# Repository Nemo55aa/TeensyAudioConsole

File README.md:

# TeensyAudioConsole
TeensyAudioConsole is a board that allows TeensyAudio to be used like a gadget such as a guitar pedal or synth module. 
I wanted to use something like that myself, and I also wanted to increase TeensyAudio's value as an instrument.
# HowtoUse
TeensyAudio's basic usage is Here:
https://www.pjrc.com/teensy/td_libs_Audio.html

# TeensyAudioConsole
TeensyAudioの，エフェクターやシンセモジュラーのようなガジェットとしての価値を高めるために作りました．
現在発注中なので，届き次第詳しい使い方についてまとめます．

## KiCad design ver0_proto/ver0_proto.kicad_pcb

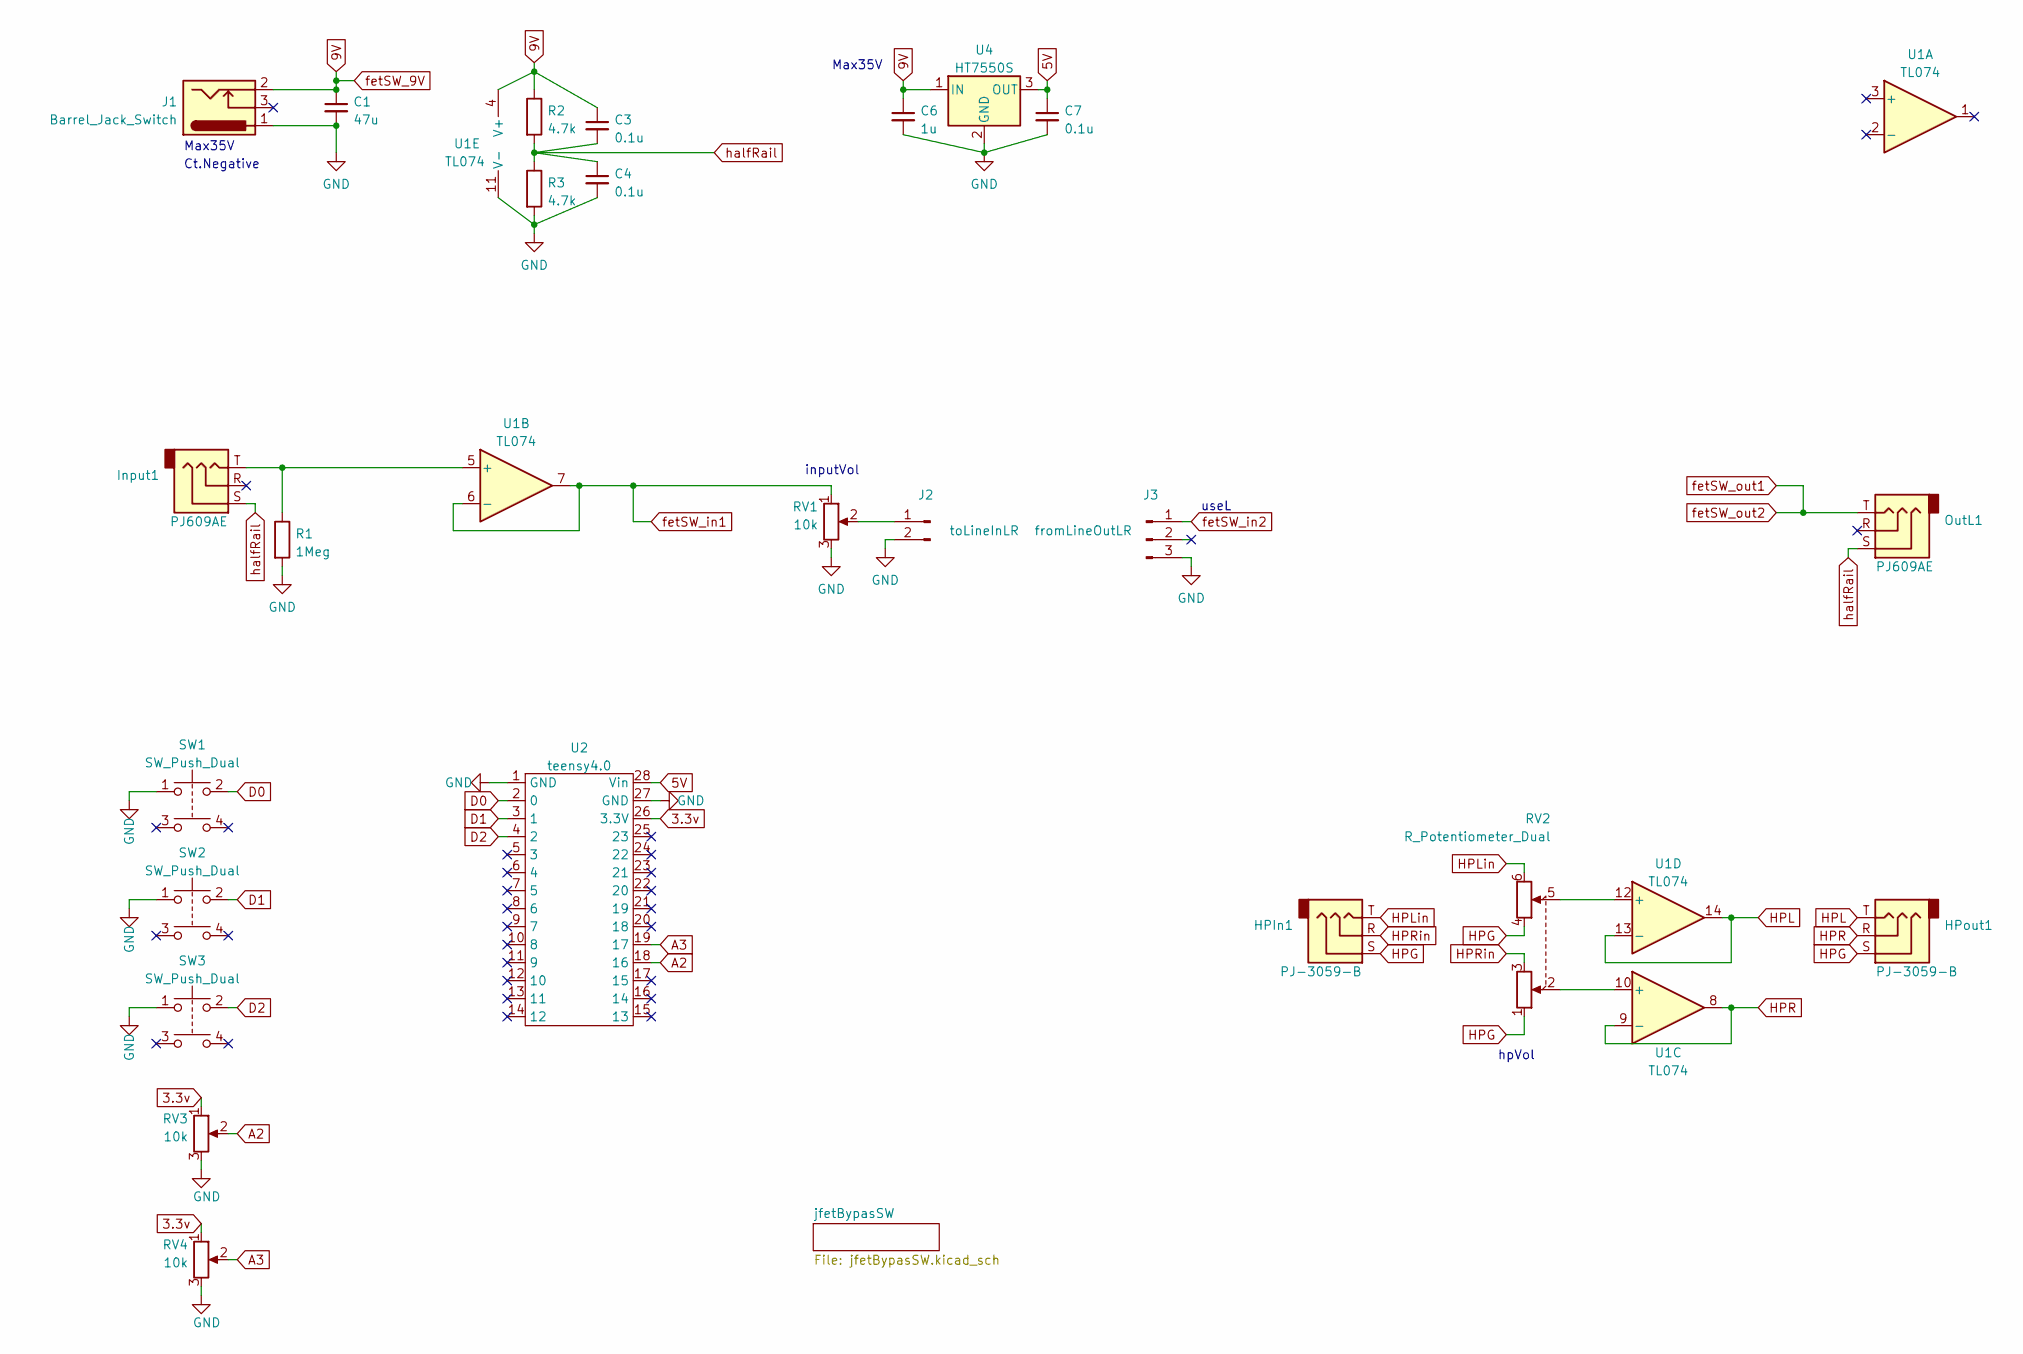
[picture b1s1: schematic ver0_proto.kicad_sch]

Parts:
C1: 47u; CP_Radial_D10.0mm_P2.50mm_P5.00mm
C3, C4, C7: 0.1u; C_0603_1608Metric_Pad1.08x0.95mm_HandSolder
C6: 1u; C_0603_1608Metric_Pad1.08x0.95mm_HandSolder
HPIn1: PJ-3059-B; AUDIO-TH_XKB_PJ-3059-B
HPout1: PJ-3059-B; AUDIO-TH_XKB_PJ-3059-B
Input1: PJ609AE; AUDIO-TH_PJ-609AE
J1: Barrel_Jack_Switch; BarrelJack_Horizontal
J2: toLineInLR; PinHeader_1x02_P2.54mm_Vertical
J3: fromLineOutLR; PinHeader_1x03_P2.54mm_Vertical
OutL1: PJ609AE; AUDIO-TH_PJ-609AE
R1: 1Meg; R_0603_1608Metric_Pad0.98x0.95mm_HandSolder
R2, R3: 4.7k; R_0603_1608Metric_Pad0.98x0.95mm_HandSolder
RV1, RV3, RV4: 10k; RES-TH_RK09K1130AAU
RV2: R_Potentiometer_Dual; RES-TH_RK14K1240036
SW1, SW2, SW3: SW_Push_Dual; SW_PUSH_6mm
U1: TL074; SO-14_3.9x8.65mm_P1.27mm
U2: teensy4.0; teensy4.0WithAudioSh
U4: HT7550S; SOT-23

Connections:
3.3v: RV3.1, RV4.1, U2.26 (3.3V)
5V: C7.1, U2.28 (Vin), U4.3 (OUT)
9V: C1.1, C3.1, C6.1, J1.2, R2.1, U1.4 (V+), U4.1 (IN); also elsewhere on the board
A2: RV3.2, U2.18 (16)
A3: RV4.2, U2.19 (17)
D0: SW1.2, U2.2 (0)
D1: SW2.2, U2.3 (1)
D2: SW3.2, U2.4 (2)
GND: C1.2, C4.2, C6.2, C7.2, J1.1, J2.2, J3.3, R1.2, R3.2, RV1.3, RV3.3, RV4.3, SW1.1, SW2.1, SW3.1, U1.11 (V-), U2.1 (GND), U2.27 (GND), U4.2 (GND); also elsewhere on the board
HPG: HPIn1.S, HPout1.S, RV2.1, RV2.4
HPL: HPout1.T, U1.13 (-), U1.14
HPLin: HPIn1.T, RV2.6
HPR: HPout1.R, U1.8, U1.9 (-)
HPRin: HPIn1.R, RV2.3
unnamed: Input1.T, R1.1, U1.5 (+)
unnamed: J2.1, RV1.2
unnamed: RV2.5, U1.12 (+)
unnamed: RV2.2, U1.10 (+)
fetSW_in1: RV1.1, U1.6 (-), U1.7; also elsewhere on the board
fetSW_in2: J3.1; also elsewhere on the board
fetSW_out1: OutL1.T; also elsewhere on the board
halfRail: C3.2, C4.1, Input1.S, OutL1.S, R2.2, R3.1

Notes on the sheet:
Max35V
useL
inputVol
hpVol
Ct.Negative

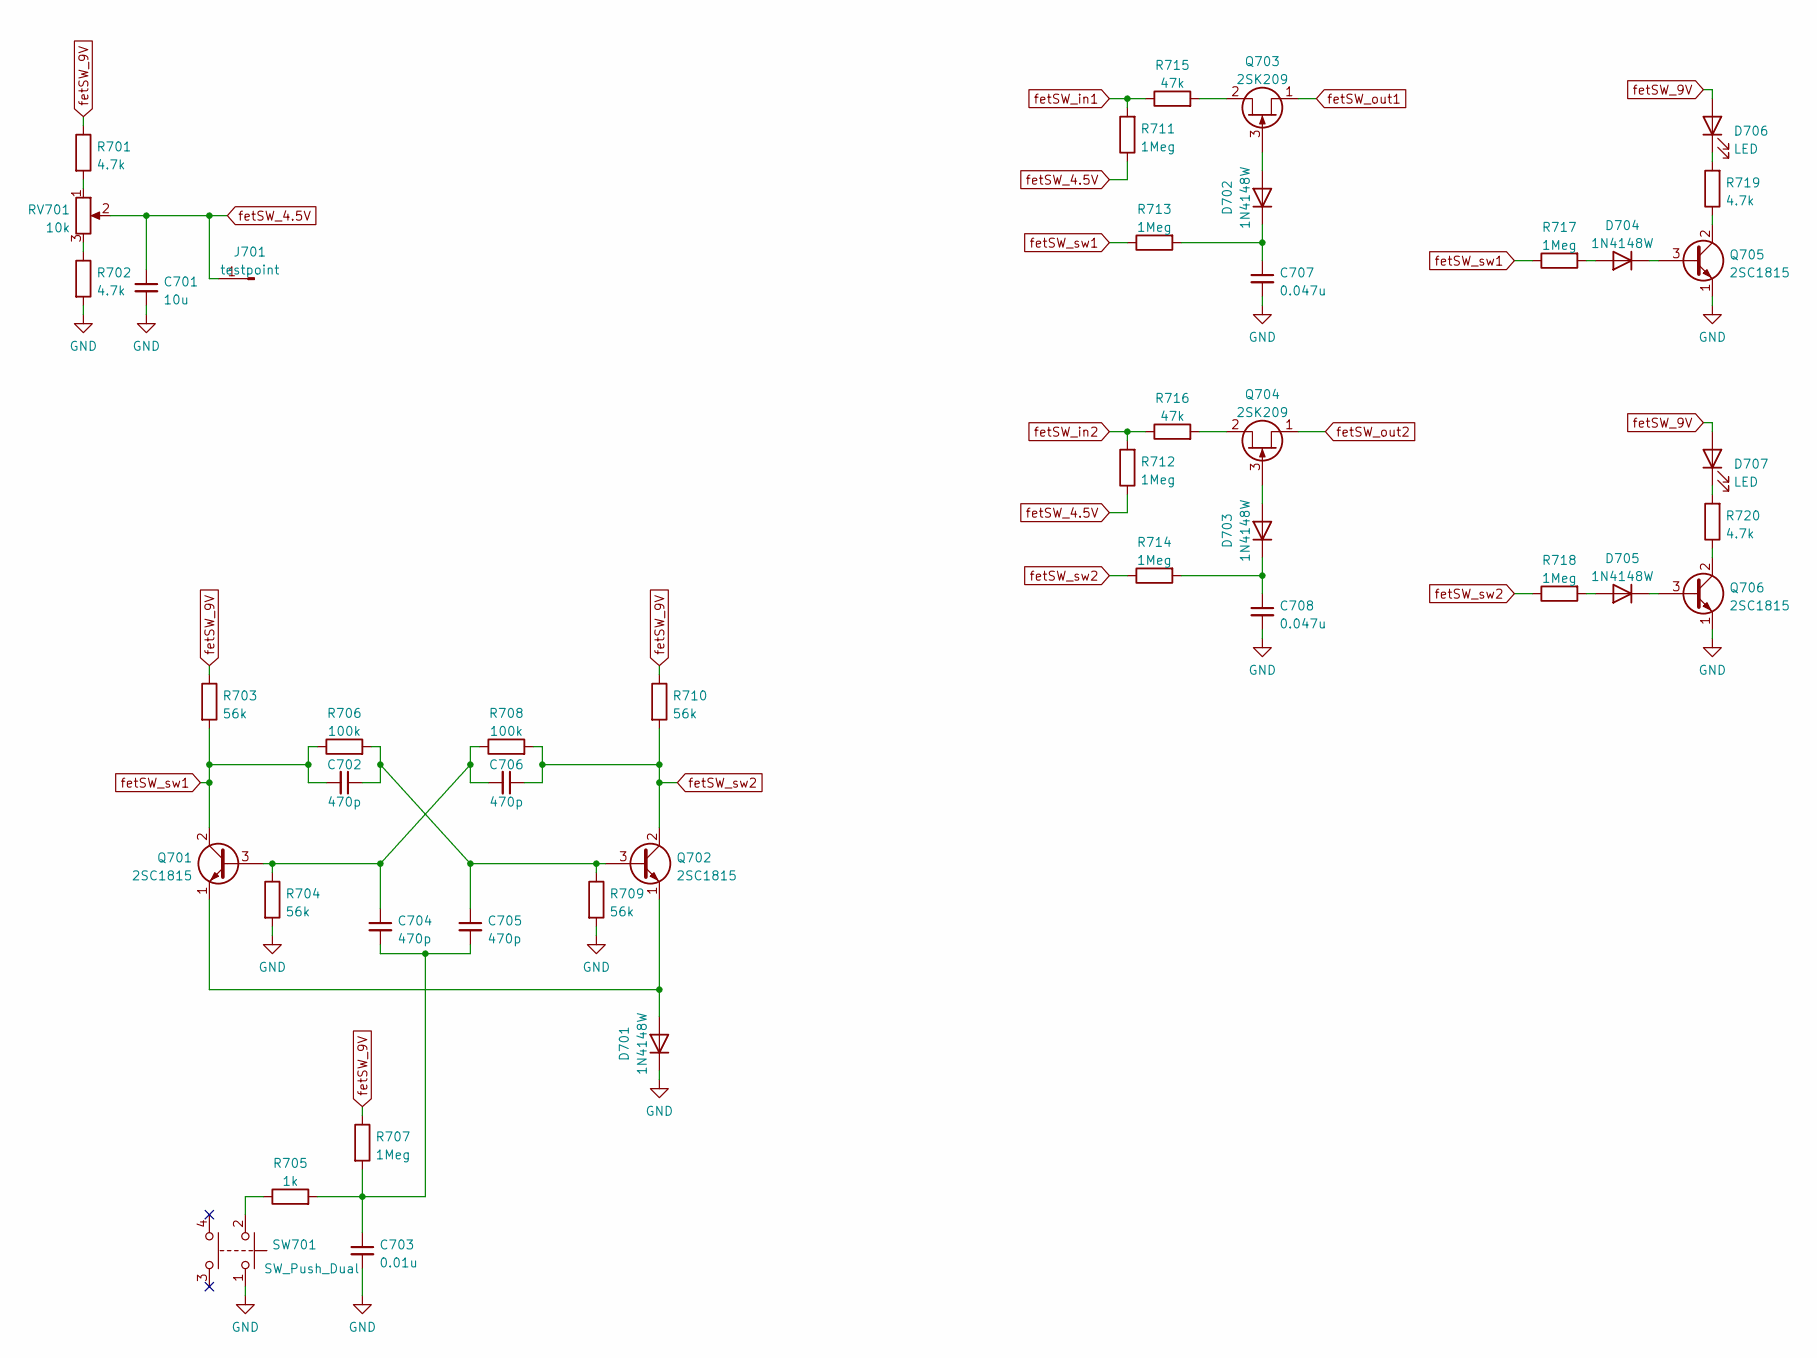
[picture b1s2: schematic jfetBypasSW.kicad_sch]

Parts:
C701: 10u; CP_Radial_D6.3mm_P2.50mm
C702, C704, C705, C706: 470p; C_0603_1608Metric_Pad1.08x0.95mm_HandSolder
C703: 0.01u; C_0603_1608Metric_Pad1.08x0.95mm_HandSolder
C707, C708: 0.047u; C_0603_1608Metric_Pad1.08x0.95mm_HandSolder
D701, D702, D703, D704, D705: 1N4148W; D_SOD-123
D706, D707: LED; LED_D3.0mm
J701: testpoint; TestPoint_Loop_D1.80mm_Drill1.0mm_Beaded
Q701, Q702, Q705, Q706: 2SC1815; SOT-23
Q703, Q704: 2SK209; SC-59_Handsoldering
R701, R702, R719, R720: 4.7k; R_0603_1608Metric_Pad0.98x0.95mm_HandSolder
R703, R704, R709, R710: 56k; R_0603_1608Metric_Pad0.98x0.95mm_HandSolder
R705: 1k; R_0603_1608Metric_Pad0.98x0.95mm_HandSolder
R706, R708: 100k; R_0603_1608Metric_Pad0.98x0.95mm_HandSolder
R707, R711, R712, R713, R714, R717, R718: 1Meg; R_0603_1608Metric_Pad0.98x0.95mm_HandSolder
R715, R716: 47k; R_0603_1608Metric_Pad0.98x0.95mm_HandSolder
RV701: 10k; Potentiometer_Bourns_3296W_Vertical
SW701: SW_Push_Dual; SW_PUSH_6mm

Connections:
9V: D706.2 (A), D707.2 (A), R701.1, R703.1, R707.1, R710.1; also elsewhere on the board
GND: C701.2, C703.2, C707.2, C708.2, D701.1 (K), Q705.1 (E), Q706.1 (E), R702.2, R704.2, R709.2, SW701.1; also elsewhere on the board
unnamed: C702.1, C705.1, Q702.3 (B), R706.2, R709.1
unnamed: C703.1, C704.2, C705.2, R705.2, R707.2
unnamed: C704.1, C706.2, Q701.3 (B), R704.1, R708.1
unnamed: C707.1, D702.1 (K), R713.2
unnamed: C708.1, D703.1 (K), R714.2
unnamed: D701.2 (A), Q701.1 (E), Q702.1 (E)
unnamed: D702.2 (A), Q703.3 (G)
unnamed: D703.2 (A), Q704.3 (G)
unnamed: D704.1 (K), Q705.3 (B)
unnamed: D704.2 (A), R717.2
unnamed: D705.1 (K), Q706.3 (B)
unnamed: D705.2 (A), R718.2
unnamed: D706.1 (K), R719.2
unnamed: D707.1 (K), R720.2
unnamed: Q703.2 (D), R715.2
unnamed: Q704.2 (D), R716.2
unnamed: Q705.2 (C), R719.1
unnamed: Q706.2 (C), R720.1
unnamed: R701.2, RV701.1
unnamed: R702.1, RV701.3
unnamed: R705.1, SW701.2
fetSW_4.5V: C701.1, J701.1, R711.1, R712.1, RV701.2
fetSW_in1: R711.2, R715.1; also elsewhere on the board
fetSW_in2: R712.2, R716.1; also elsewhere on the board
fetSW_out1: Q703.1 (S), Q704.1 (S); also elsewhere on the board
fetSW_sw1: C702.2, Q701.2 (C), R703.2, R706.1, R713.1, R717.1
fetSW_sw2: C706.1, Q702.2 (C), R708.2, R710.2, R714.1, R718.1

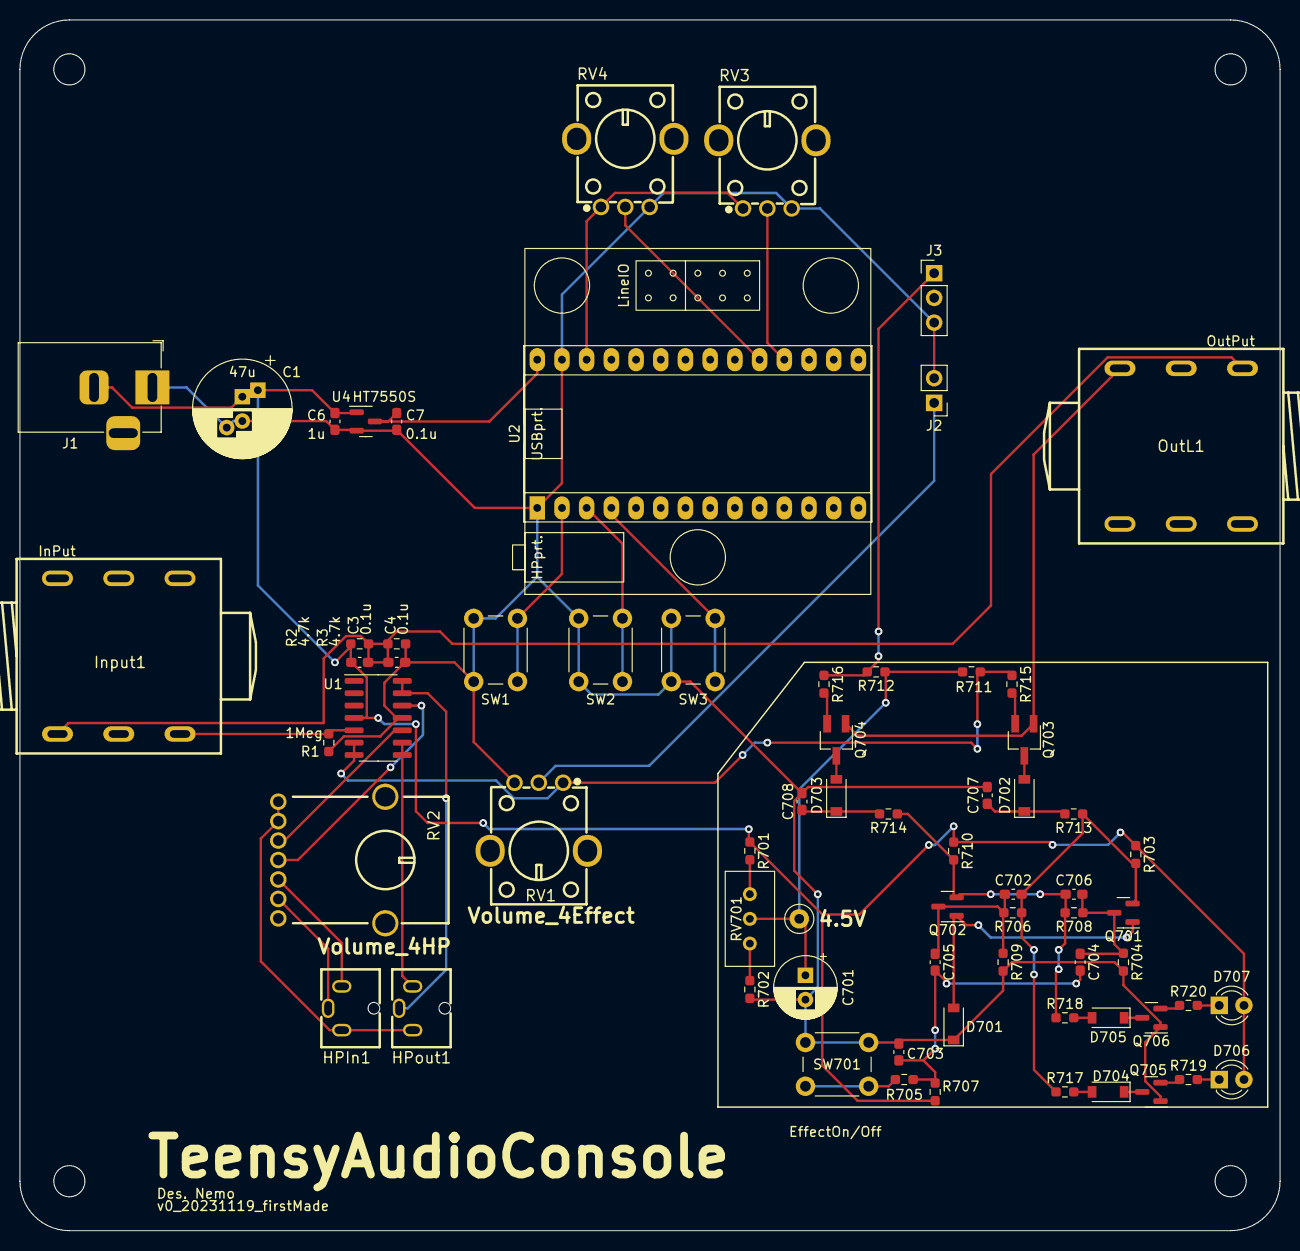
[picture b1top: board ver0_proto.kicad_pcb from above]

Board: 2 copper layers, 129.5 x 124.5 mm, 69 parts (0 on the bottom side), 46 nets.

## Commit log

2023-11-19 FirstMade
    Added kicad6 Project including schematic, pcb.
